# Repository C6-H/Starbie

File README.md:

# Starbie (Ghosty)
PCB week Hack Club Half Life
Guided Project (Starbie) turned nerdy reference covered tamagotchi like interactable toy.
Started as the Starbie guided project, still mostly that, but with some tweaks.
Built as week 1 project, but also to learn a bit about PCBs and electronics

A tamagotchi style PCB pet that you can interact with by physicially moving the board and by pressing buttons. I used a ghost sprite for the pet, but this can be changed if wanted.

Component schematics made in KiCad with help from the project guide.
Schematics in StarbiePCB folder (StarbiePCB.kicad_sch.Ick
ESP32 for processing, 8 and 4 pin for screen and motion sensor and DTH for enviromnent readings and buttons for menu selection

PCB then also edited in KiCad, changed the shape of the PCB to a non-descript triangle shape, routed the traces, and added some things to the board to truly make it my own.
Gerber and Drill files are included in GerberAndDrills folder

The Screen, buttons, motion sensor, ESP32 and DHT-11 will be pegged into their places in the PCB once it has been manufactured.

Then for the firmware I just used the firmware supplied in the project folder, but to customize it a bit I changed the sprite to a custom made ghost sprite.

Edit this bit array to change the sprite of the pet

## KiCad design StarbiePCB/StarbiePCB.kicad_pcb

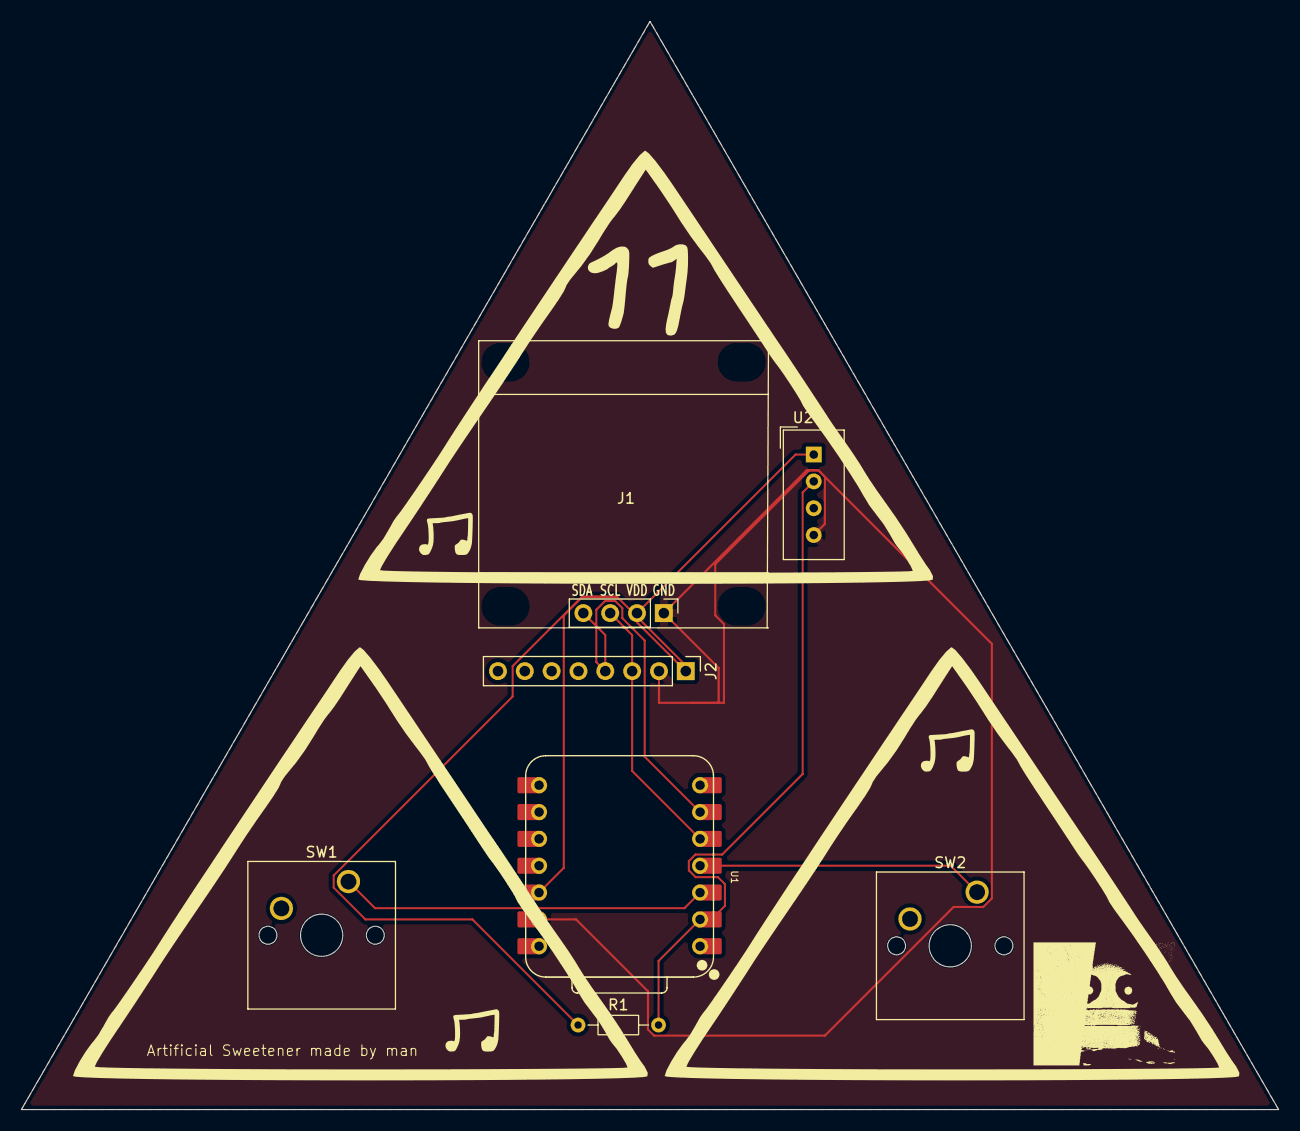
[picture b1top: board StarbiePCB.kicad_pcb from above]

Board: 2 copper layers, 119.0 x 103.0 mm, 7 parts (0 on the bottom side), 7 nets.

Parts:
J1: Conn_01x04_Pin; Display_128x64_096_I2C
J2: Conn_01x08_Pin; PinHeader_1x08_P2.54mm_Vertical
R1: 10k; R_Axial_DIN0204_L3.6mm_D1.6mm_P7.62mm_Horizontal
SW1, SW2: SW_Push; SW_Cherry_MX_1.00u_PCB
U1: XIAO-ESP32-C3-SMD; XIAO-ESP32-C6-DIP
U2: DHT11; Aosong_DHT11_5.5x12.0_P2.54mm

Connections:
+3.3V: J1.2, J2.1, R1.1, U1.12 (3V3_OUT), U2.1 (VDD)
/DHT11 DATA: R1.2, U1.2 (D1), U2.2 (DATA)
/GP102: SW1.1 (1_1), U1.3 (D2)
/GP103: SW2.1 (1_1), U1.4 (D3)
/SCL: J1.3, J2.3, U1.5 (D4)
/SDA: J1.4, J2.4, U1.6 (D5)
GND: J1.1, J2.2, U1.13 (GND), U2.4 (GND)
